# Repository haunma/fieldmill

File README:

# Field mill

Work in progress...

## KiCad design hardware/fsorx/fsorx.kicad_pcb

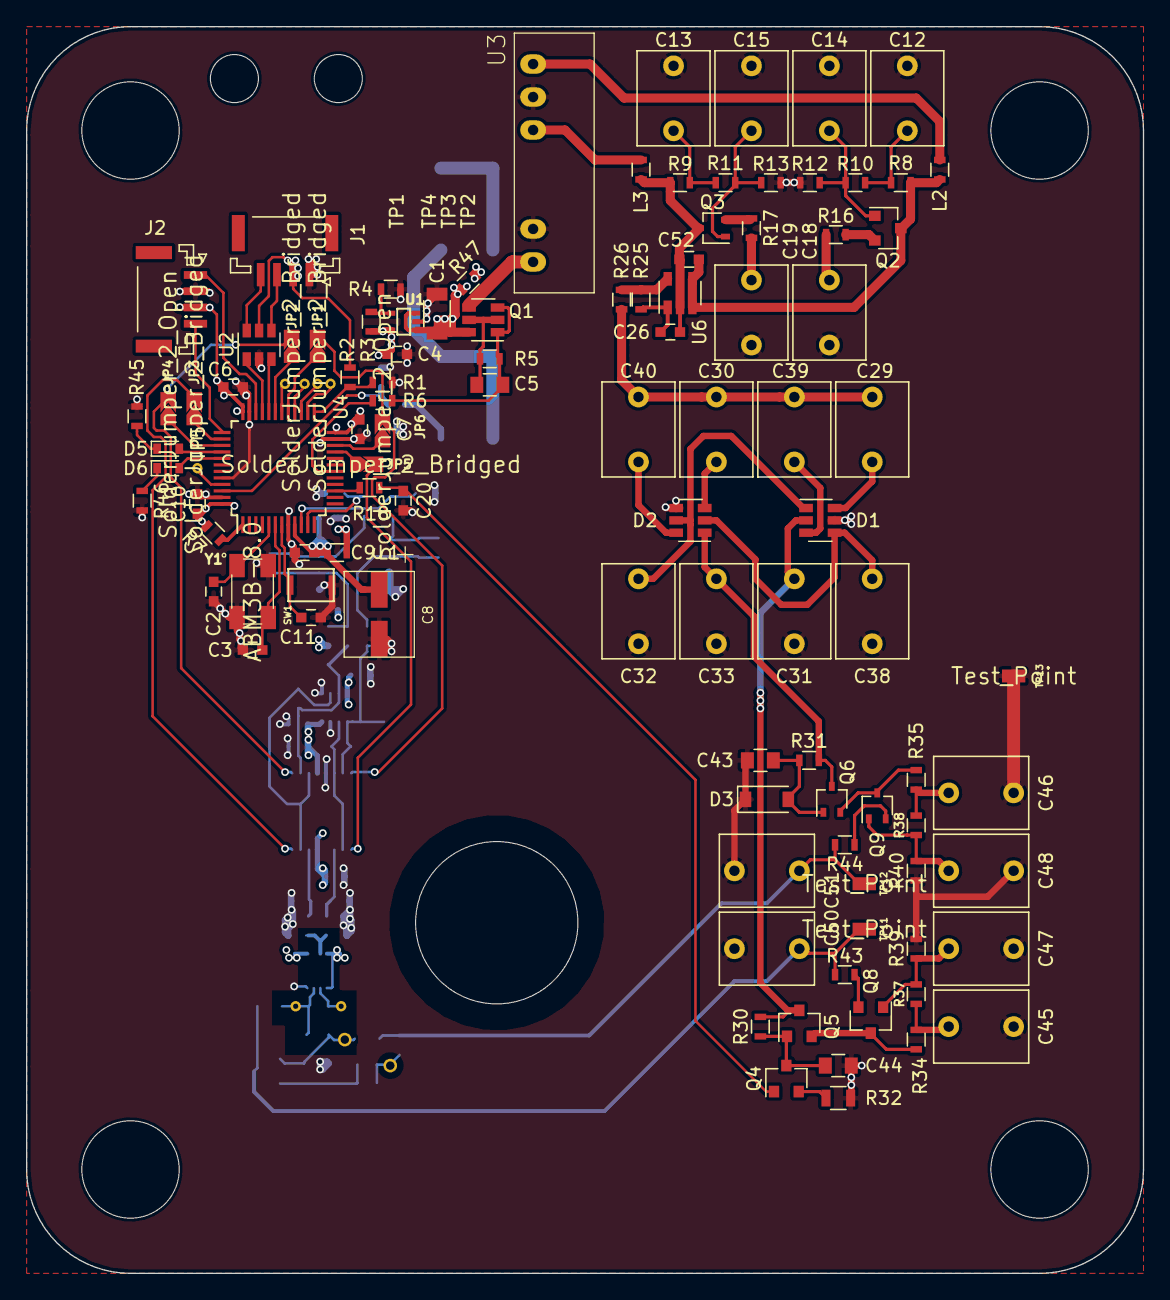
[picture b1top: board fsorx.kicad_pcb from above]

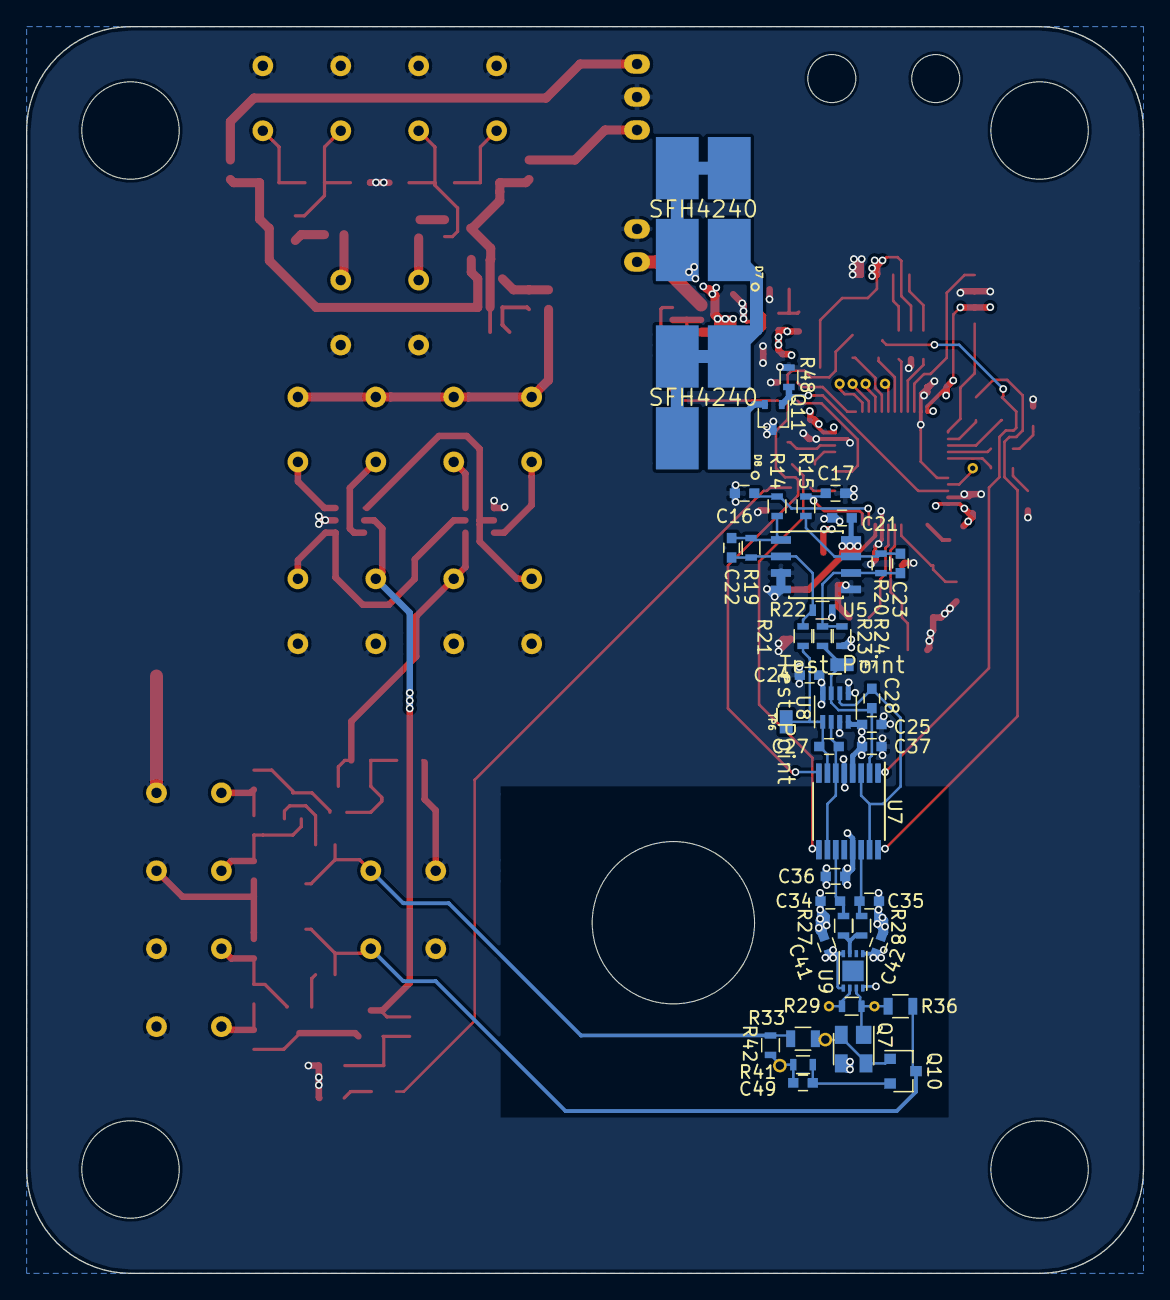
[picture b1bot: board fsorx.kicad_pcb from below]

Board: 4 copper layers, 86.0 x 96.0 mm, 161 parts (46 on the bottom side), 99 nets.

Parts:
C1: 10u; C_1206
C2, C3, C22, C23: 10p; C_0603
C4, C20: 1u; C_0603
C5: 1u; C_0805
C6, C7, C9, C10, C11, C21, C24, C25, C36, C37, C41, C42, C52: 100n; C_0603
C8: 10u electrolytic; Panasonic_ECEV1CA220P
C12, C13, C14, C15, C18, C19, C29, C30, C31, C32, C33, C38, C39, C40, C45, C46, C47, C48, C50, C51: 1u; C_Rect_L7.2mm_W5.5mm_P5.00mm_FKS2_FKP2_MKS2_MKP2
C16, C17: 470p; C_0603
C26: 220p; C_0603
C27, C28: 120p; C_0603
C34, C35: 68p; C_0603
C43, C44: 4.7n; C_0805
C49: DNI; C_0603
D1, D2: SD103ASDM; SOT-23-6
D3: BZT52C27; D_SOD-123
D5: SAT; D_0603
D6: LOCK; D_0603
D7, D8: SFH4240; OSRAM_SFH4240
J1: USB; JST_GH_SM04B-GHS-TB_04x1.25mm_Angled
J2: JTAG SWD; JST_GH_SM04B-GHS-TB_04x1.25mm_Angled
JP1, JP2, JP3, JP5: SolderJumper_2_Bridged; Solder_Bridge
JP4, JP6: SolderJumper_2_Open; Solder_Bridge
L1, L2, L3: FB; R_0603
MK1, MK2, MK3, MK4: Suction cup; MountingHole_7.5mm
MK5: Photodiode; MountingHole_TO8
MK6, MK7: USB strain relief; MountingHole_3.7mm
Q1: DMP2240UDM; SOT-23-6
Q2, Q5, Q8: MMBT6429; SOT-23
Q3, Q6, Q9: BC858C; SOT-323_SC-70
Q4: MMBT3904; SOT-23
Q7: BFG25A/X; SOT-143
Q10: MMBT6429: DNI; SOT-23
Q11: BSS214NW; SOT-323_SC-70
R1: 620k; R_0603
R2: 430k; R_0603
R3: 562k; R_0603
R4: 158k; R_0603
R5: 470k; R_0603
R6, R25: 47k; R_0603
R7, R42: 0; R_0603
R8, R9, R10, R11, R34, R35, R37, R38: 4.7k; R_0603
R12: 18.7k; R_0603
R13: 21.5k; R_0603
R14, R15, R26: 100; R_0603
R16, R17, R47: 10; R_0603
R18, R43, R44: 10k; R_0603
R19, R20, R21, R23: 2.94k; R_0603
R22, R24: 8.2k; R_0603
R27, R28: 680; R_0603
R29: 820k low noise; R_0603
R30, R31: 1M; R_0603
R32: 130k; R_0805
R33: 1.2M low noise; R_0805
R36: 680k low noise; R_0805
R39, R40, R41: DNI; R_0603
R45, R46: TBD; R_0603
R48: 100k; R_0603
SW1: Reset; CK_KXT3_switch
TP: Test_Point; SolderWirePad_single_0-65mmDrill
TP1, TP2, TP3, TP4, TP5, TP9, TP10: Test_Point; SolderWirePad_single_0-4mmDrill
TP6, TP7, TP11, TP12, TP13: Test_Point; KOA_Speer_RCU_testpad
TP#2: Test_Point; SolderWirePad_single_0-65mmDrill
U1: TPS71701DCK; SC70-5
U2: USBLC6-2; SOT-23-6
U3: MEV1D0509SC; Murata_MEV1DxxxxSC
U4: STM32L433Cx; LQFP-48_7x7mm_Pitch0.5mm
U5: ADA4891-2; SOIC-8_3.9x4.9mm_Pitch1.27mm
U6: MIC1557; SOT-23-5
U7: ADG611; TSSOP-16_4.4x5mm_Pitch0.65mm
U8: AD8034; SOT-23-8
U9: ADA4817-1; LFCSP-8-1EP_2x3mm_Pitch0.5mm
Y1: ABM3B-8.0; Abracon_ABM3B

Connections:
+3.6V: C4.2, C6.1, C7.1, C10.1, J2.3, L1.2, R3.2, R7.2, U1.5, U4.24, U4.36, U4.48
+5V: C18.2, C24.1, C36.2, C41.1, R16.1, U7.13, U8.8, U9.1, U9.8
-5V: C19.1, C25.1, C37.2, C42.1, R17.1, R22.1, R24.1, U7.4, U8.4, U9.5
GND: C1.1, C2.1, C3.1, C4.1, C6.2, C7.2, C8.2, C9.2, C10.2, C11.2, C12.1, C13.2, C14.1, C15.2, C16.1, C17.1, C18.1, C19.2, C20.1, C21.1, C24.2, C25.2, C31.2, C32.2, C33.1, C34.1, C35.1, C36.1, C37.1, C38.1, C41.2, C42.2, C43.1, C44.1, C45.1, C46.2, C47.1, C48.2, C50.1, C51.2, D1.5, D2.4, D3.1, J1.1, J2.2, Q7.3, Q11.3, R1.1, R4.1, R12.1, R13.2, R32.1, R39.1, R40.2, R45.1, R46.1, R48.2, SW1.1, TP13.1, U1.2, U2.2, U3.2, U3.6, U4.8, U4.23, U4.35, U4.44, U4.47, U5.3, U5.4, U5.5, U7.5, U8.3, U8.5, U9.4, Y1.2, Y1.4
unnamed: C2.2, U4.5, Y1.1
unnamed: C3.2, U4.6, Y1.3
unnamed: C5.1, Q1.1, Q1.3, R5.1, R6.2
unnamed: C5.2, Q1.2, Q1.5, R5.2
unnamed: C11.1, SW1.2, U4.7
unnamed: C12.2, R8.2, R10.2
unnamed: C13.1, R9.2, R11.2
unnamed: C14.2, Q2.1, R10.1, R12.2
unnamed: C15.1, Q3.1, R11.1, R13.1
unnamed: C16.2, R14.2, U4.10
unnamed: C17.2, R15.2, U4.11
unnamed: C22.1, R14.1, R19.2, U5.1
unnamed: C22.2, R19.1, R21.2, R22.2, U5.2
unnamed: C23.1, R15.1, R20.2, U5.7
unnamed: C23.2, R20.1, R23.2, R24.2, U5.6
unnamed: C26.1, R25.1, U6.1
unnamed: C26.2, C52.1, L3.2, Q3.3, R9.1, U6.2
unnamed: C27.1, U7.6, U7.10, U8.2
unnamed: C27.2, R21.1, TP6.1, U7.7, U8.1
unnamed: C28.1, U7.3, U7.15, U8.6
unnamed: C28.2, R23.1, TP7.1, U7.2, U8.7
unnamed: C29.1, D1.6
unnamed: C29.2, C30.2, C39.1, C40.1, R26.1
unnamed: C30.1, D2.3
unnamed: C31.1, D1.2, Q5.3, R30.1
unnamed: C32.1, D1.1, D2.5
unnamed: C33.2, D2.1, Q6.3, R31.1
unnamed: C34.2, R27.2, U7.11
unnamed: C35.2, R28.2, U7.14
unnamed: C38.2, D1.4, D2.2
unnamed: C39.2, D1.3
unnamed: C40.2, D2.6
unnamed: C43.2, D3.2, Q6.1, R31.2
unnamed: C44.2, Q4.3, Q5.1, R30.2
unnamed: C45.2, R34.2, R37.2
unnamed: C46.1, R35.2, R38.2
unnamed: C47.2, Q8.1, R37.1, R39.2
unnamed: C48.1, Q9.1, R38.1, R40.1
unnamed: C49.1, R41.2, R42.1, TP.1
unnamed: C49.2, Q10.2, R41.1
unnamed: C52.2, L2.2, Q2.3, R8.1, U6.3, U6.4
unnamed: Q7.2, Q7.4, Q10.1, R33.1, TP#2.1
unnamed: D5.1, R45.2
unnamed: D5.2, U4.40
unnamed: D6.1, R46.2
unnamed: D6.2, U4.41
unnamed: D7.1, D8.2, D8.3, D8.4
unnamed: D7.2, D7.3, D7.4, R47.1
unnamed: D8.1, Q11.2
unnamed: J1.3, U2.4
unnamed: J1.4, U2.6
unnamed: J2.1, U4.34
unnamed: J2.4, U4.37
unnamed: JP1.1, U4.29
unnamed: JP2.1, U4.31
unnamed: JP3.1, U4.38
unnamed: JP4.1, U4.39
unnamed: JP5.1, U4.21
unnamed: JP6.1, U4.22
unnamed: L2.1, U3.7
unnamed: L3.1, U3.5
unnamed: Q1.4, U3.1
unnamed: Q2.2, R16.2
unnamed: Q3.2, R17.2
unnamed: Q4.2, R32.2
unnamed: Q5.2, Q8.3, R34.1
unnamed: Q6.2, Q9.3, R35.1
unnamed: Q7.1, R29.2, R36.1, TP10.1, U9.3
unnamed: Q8.2, R43.2
unnamed: Q9.2, R44.2
unnamed: Q11.1, R48.1, U4.46
unnamed: R1.2, R2.2, U4.25
unnamed: R3.1, R4.2, U1.4
unnamed: R6.1, U4.18
unnamed: R7.1, U4.1
unnamed: R18.2, U4.15
unnamed: R25.2, R26.2, U6.5
unnamed: R27.1, R28.1, U9.7
unnamed: R29.1, TP9.1, U9.2
unnamed: TP1.1, U4.30
unnamed: TP2.1, U4.26
unnamed: TP3.1, U4.27
unnamed: TP4.1, U4.28
unnamed: TP5.1, U4.45
unnamed: U2.1, U4.33
unnamed: U2.3, U4.32
VBUS: C1.2, J1.2, Q1.6, R2.1, R47.2, U1.1, U1.3, U2.5
VDDA: C8.1, C9.1, C21.2, L1.1, U4.9, U5.8
Vbias+: C50.2, Q10.3, R36.2, R43.1, TP11.1
Vbias-: C51.1, R33.2, R42.2, R44.1, TP12.1
VbiasCtl: C20.2, Q4.1, R18.1
~INT_A: JP5.2, U7.9
~INT_B: JP3.2, U7.16
~RESET_A: JP1.2, JP6.2, U7.8
~RESET_B: JP2.2, JP4.2, U7.1

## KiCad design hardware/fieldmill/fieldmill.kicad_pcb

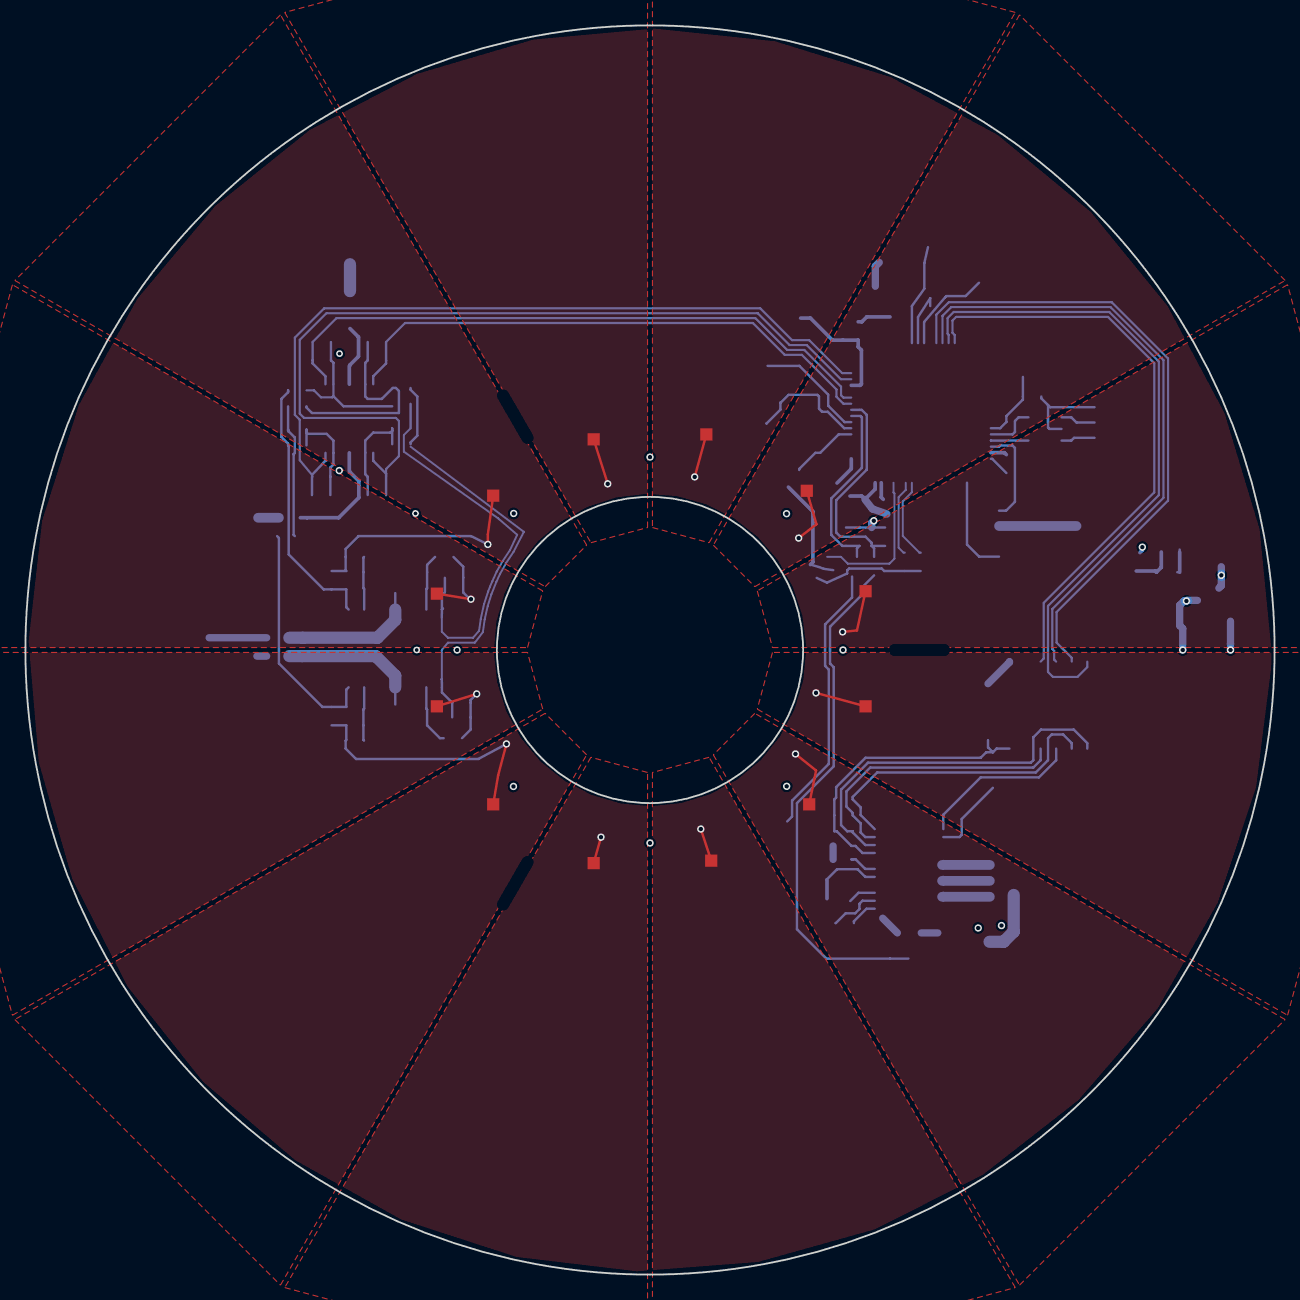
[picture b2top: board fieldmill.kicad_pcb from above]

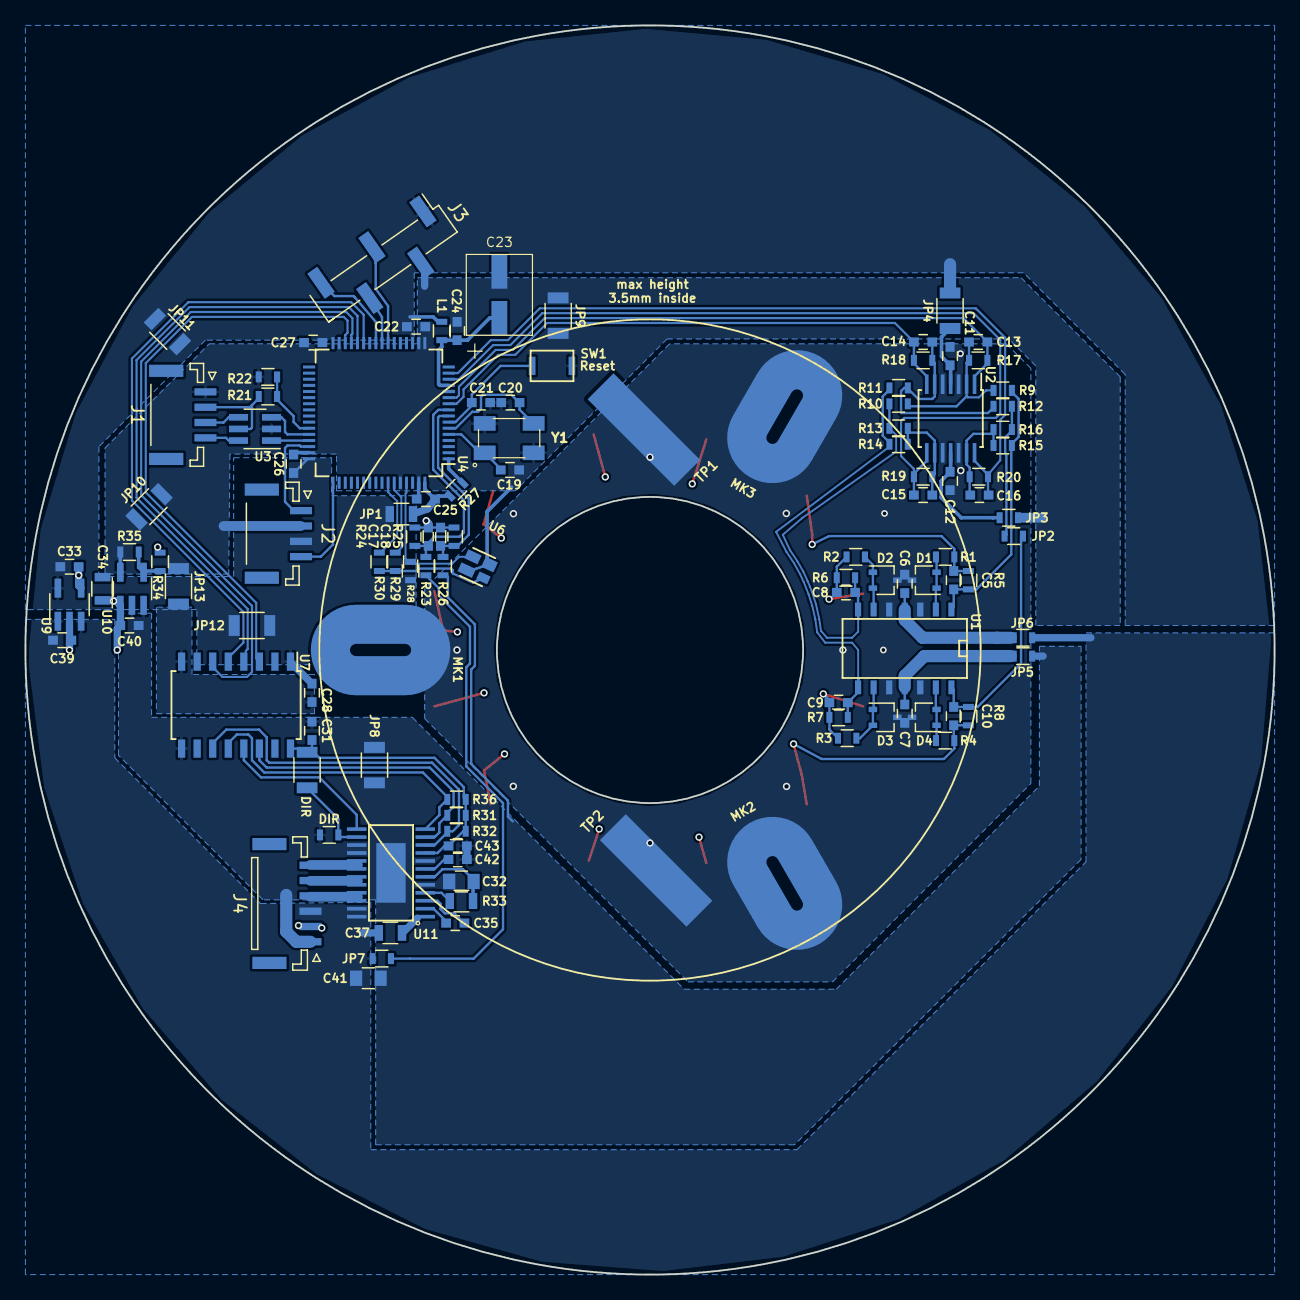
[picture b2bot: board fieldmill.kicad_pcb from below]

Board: 4 copper layers, 102.0 x 102.0 mm, 112 parts (111 on the bottom side), 72 nets.

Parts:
C5, C8, C9, C10: 220p; C_0603
C6, C7, C11, C12, C17, C18, C21, C22, C24, C25, C26, C27, C28, C31, C35: 100n; C_0603
C13, C14, C15, C16: 10n; C_0603
C19, C20: 10p; C_0603
C23: 10u electrolytic; Panasonic_ECEV1CA220P
C32, C41: 10u; C_0805
C33: 2.2u; C_0603
C34: 2.2u; R_0805
C37: 100n; R_0805
C39, C40, C42, C43: 1u; C_0603
D1, D2, D3, D4: BAV199; SOT-323_SC-70
J1: USB debug; JST_GH_SM04B-GHS-TB_04x1.25mm_Angled
J2: JTAG SWD; JST_GH_SM04B-GHS-TB_04x1.25mm_Angled
J3: Optical Comms; Pin_Header_Straight_1x05_Pitch2.54mm_SMD_Pin1Left
J4: Battery (2x 18650), BLDC motor; JST_GH_BM06B-GHS-TBT_06x1.25mm_Straight
JP1: 0805 hop; R_0805
JP2, JP3, JP5, JP6, JP7: 0603 hop; R_0603
JP4, JP8, JP9, JP10, JP11, JP12, JP13: 1206 hop; R_1206
L1: FB; R_0603
MK1, MK2, MK3: Mounting holes; Wurth_9771050360R
R1, R2, R3, R4: 47k; R_0603
R5, R6, R7, R8: 47M; R_0603
R9, R10, R11, R12, R13, R14, R15, R16: 12k; R_0603
R17, R18, R19, R20: 3k; R_0603
R21: 620k; R_0603
R22: 430k; R_0603
R23, R26: 2M; R_0603
R24, R25: 1M; R_0603
R27, R38: 0; R_0603
R28, R31, R32, R36: 10k; R_0603
R29: 330; R_0603
R30: 180; R_0603
R33: 39; R_0805
R34: 22.1k; R_0603
R35: 11.5k; R_0603
R37: 0; R_1206
SW1: Reset; CK_KXT3_switch
TP1: Brush pads; brush_pad
TP2: Brush pad; brush_pad
U1: OPA4197; SOIC-14_N
U2: TLV4376; TSSOP14
U3: USBLC6-2; SOT-23-6_Handsoldering
U4: STM32L496RxT; LQFP-64_10x10mm_Pitch0.5mm
U6: Vishay_VCNT2020
U7: Si8605; SOIC-16W_5.3x10.2mm_Pitch1.27mm
U9: TLV700xx; SOT-23-5_HandSoldering
U10: TPS72301; SOT-23-5_HandSoldering
U11: DRV10975Z; TSSOP24_EP
Y1: ABM3B-8.0; Abracon_ABM3B
Z1: mill_sensor

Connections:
+1.8V: C22.1, C25.1, C26.1, C27.1, C28.2, C33.2, J2.3, J3.1, JP1.1, JP1.2, JP4.1, JP11.1, JP11.2, JP12.1, JP12.2, L1.2, R27.1, R28.2, U4.19, U4.32, U4.48, U4.64, U7.1, U9.5
-1.8V: C19.2, C20.2, C21.2, C22.2, C23.2, C24.2, C25.2, C26.2, C27.2, C28.1, C34.1, J1.1, J2.2, J3.2, JP3.1, JP9.1, JP9.2, JP10.1, JP10.2, JP13.1, JP13.2, R21.2, R35.1, SW1.1, U3.2, U4.12, U4.17, U4.18, U4.31, U4.47, U4.60, U4.63, U6.1, U6.4, U7.8, U10.5, Y1.2, Y1.4
/a: C5.1, R5.1, R9.2, R15.2, U1.1
/b: C8.1, R6.1, R10.2, R13.2, U1.7
/c: C9.1, R7.1, R11.2, R14.2, U1.8
/d: C10.1, JP2.1, R8.1, U1.14
B+: C37.2, C39.2, C41.1, J4.3, JP6.1, JP7.1, JP7.2, R23.2, U9.1, U9.3, U11.23, U11.24
B-: C31.1, C32.2, C40.1, C41.2, C42.1, C43.1, J4.1, JP5.1, JP8.1, JP8.2, R26.1, R38.2, U7.9, U10.2, U10.3, U11.5, U11.8, U11.15, U11.16, U11.25
GND: C6.2, C7.2, C11.2, C12.2, C17.1, C18.2, C33.1, C34.2, C39.1, C40.2, D1.3, D2.3, D3.3, D4.3, J4.2, MK1.1, MK2.1, MK3.1, R24.1, R25.2, R34.2, TP1.1, TP2.1, U1.3, U1.5, U1.10, U1.12, U2.3, U2.5, U2.10, U2.12, U9.2, U9.4, U10.1
unnamed: C5.2, R1.2, R5.2, Z1.1, Z1.5, Z1.9
unnamed: C6.1, JP6.2, U1.4
unnamed: C7.1, JP5.2, U1.11
unnamed: C8.2, R2.2, R6.2, Z1.2, Z1.6, Z1.10
unnamed: C9.2, R3.2, R7.2, Z1.3, Z1.7, Z1.11
unnamed: C10.2, R4.2, R8.2, Z1.4, Z1.8, Z1.12
unnamed: C11.1, JP4.2, U2.4
unnamed: C12.1, JP3.2, U2.11
unnamed: C13.1, R17.1, U2.1, U4.11
unnamed: C13.2, R9.1, R10.1, R17.2, U2.2
unnamed: C14.1, R18.1, U2.7, U4.10
unnamed: C14.2, R11.1, R12.1, R18.2, U2.6
unnamed: C15.1, R19.1, U2.8, U4.14
unnamed: C15.2, R13.1, R14.1, R19.2, U2.9
unnamed: C16.1, R20.1, U2.14, U4.15
unnamed: C16.2, R15.1, R16.1, R20.2, U2.13
unnamed: C17.2, R23.1, R24.2, U4.9
unnamed: C18.1, R25.1, R26.2, U4.8
unnamed: C19.1, U4.5, Y1.1
unnamed: C20.1, U4.6, Y1.3
unnamed: C21.1, SW1.2, U4.7
unnamed: C23.1, C24.1, L1.1, U4.13
unnamed: C32.1, R33.2, U11.6
unnamed: C35.1, U11.3
unnamed: C35.2, U11.2
unnamed: C37.1, U11.1
unnamed: C42.2, U11.7
unnamed: D1.1, D1.2, R1.1, U1.2
unnamed: D2.1, D2.2, R2.1, U1.6
unnamed: D3.1, D3.2, R3.1, U1.9
unnamed: D4.1, D4.2, R4.1, U1.13
unnamed: J1.2, R22.1, U3.5
unnamed: J1.3, U3.4
unnamed: J1.4, U3.6
unnamed: J2.1, U4.46
unnamed: J2.4, U4.49
unnamed: J3.3, U4.23
unnamed: J3.4, U4.24
unnamed: J3.5, U4.25
unnamed: J4.4, U11.21, U11.22
unnamed: J4.5, U11.19, U11.20
unnamed: J4.6, U11.17, U11.18
unnamed: JP2.2, R12.2, R16.2
unnamed: R21.1, R22.2, U4.43
unnamed: R27.2, U4.1
unnamed: R28.1, U4.61, U6.2
unnamed: R29.1, U4.59
unnamed: R29.2, R30.2, U6.3
unnamed: R30.1, U4.58
unnamed: R31.2, U7.14, U11.11
unnamed: R32.2, U7.11, U11.10
unnamed: R33.1, U11.4
unnamed: R34.1, R35.2, U10.4
unnamed: R36.2, U7.12, U11.12
unnamed: R37.2, R38.1, U11.14
unnamed: U3.1, U4.45
unnamed: U3.3, U4.44
unnamed: U4.27, U7.5
unnamed: U4.28, U7.4
unnamed: U4.29, U7.6
unnamed: U4.30, U7.3
unnamed: U7.13, U11.13
V3P3: C31.2, C43.2, R31.1, R32.1, R36.1, R37.1, U7.16, U11.9

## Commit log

2019-08-28 Initial commit of WIP
2019-08-28 Add license and readme
2019-08-28 Make README markdown
